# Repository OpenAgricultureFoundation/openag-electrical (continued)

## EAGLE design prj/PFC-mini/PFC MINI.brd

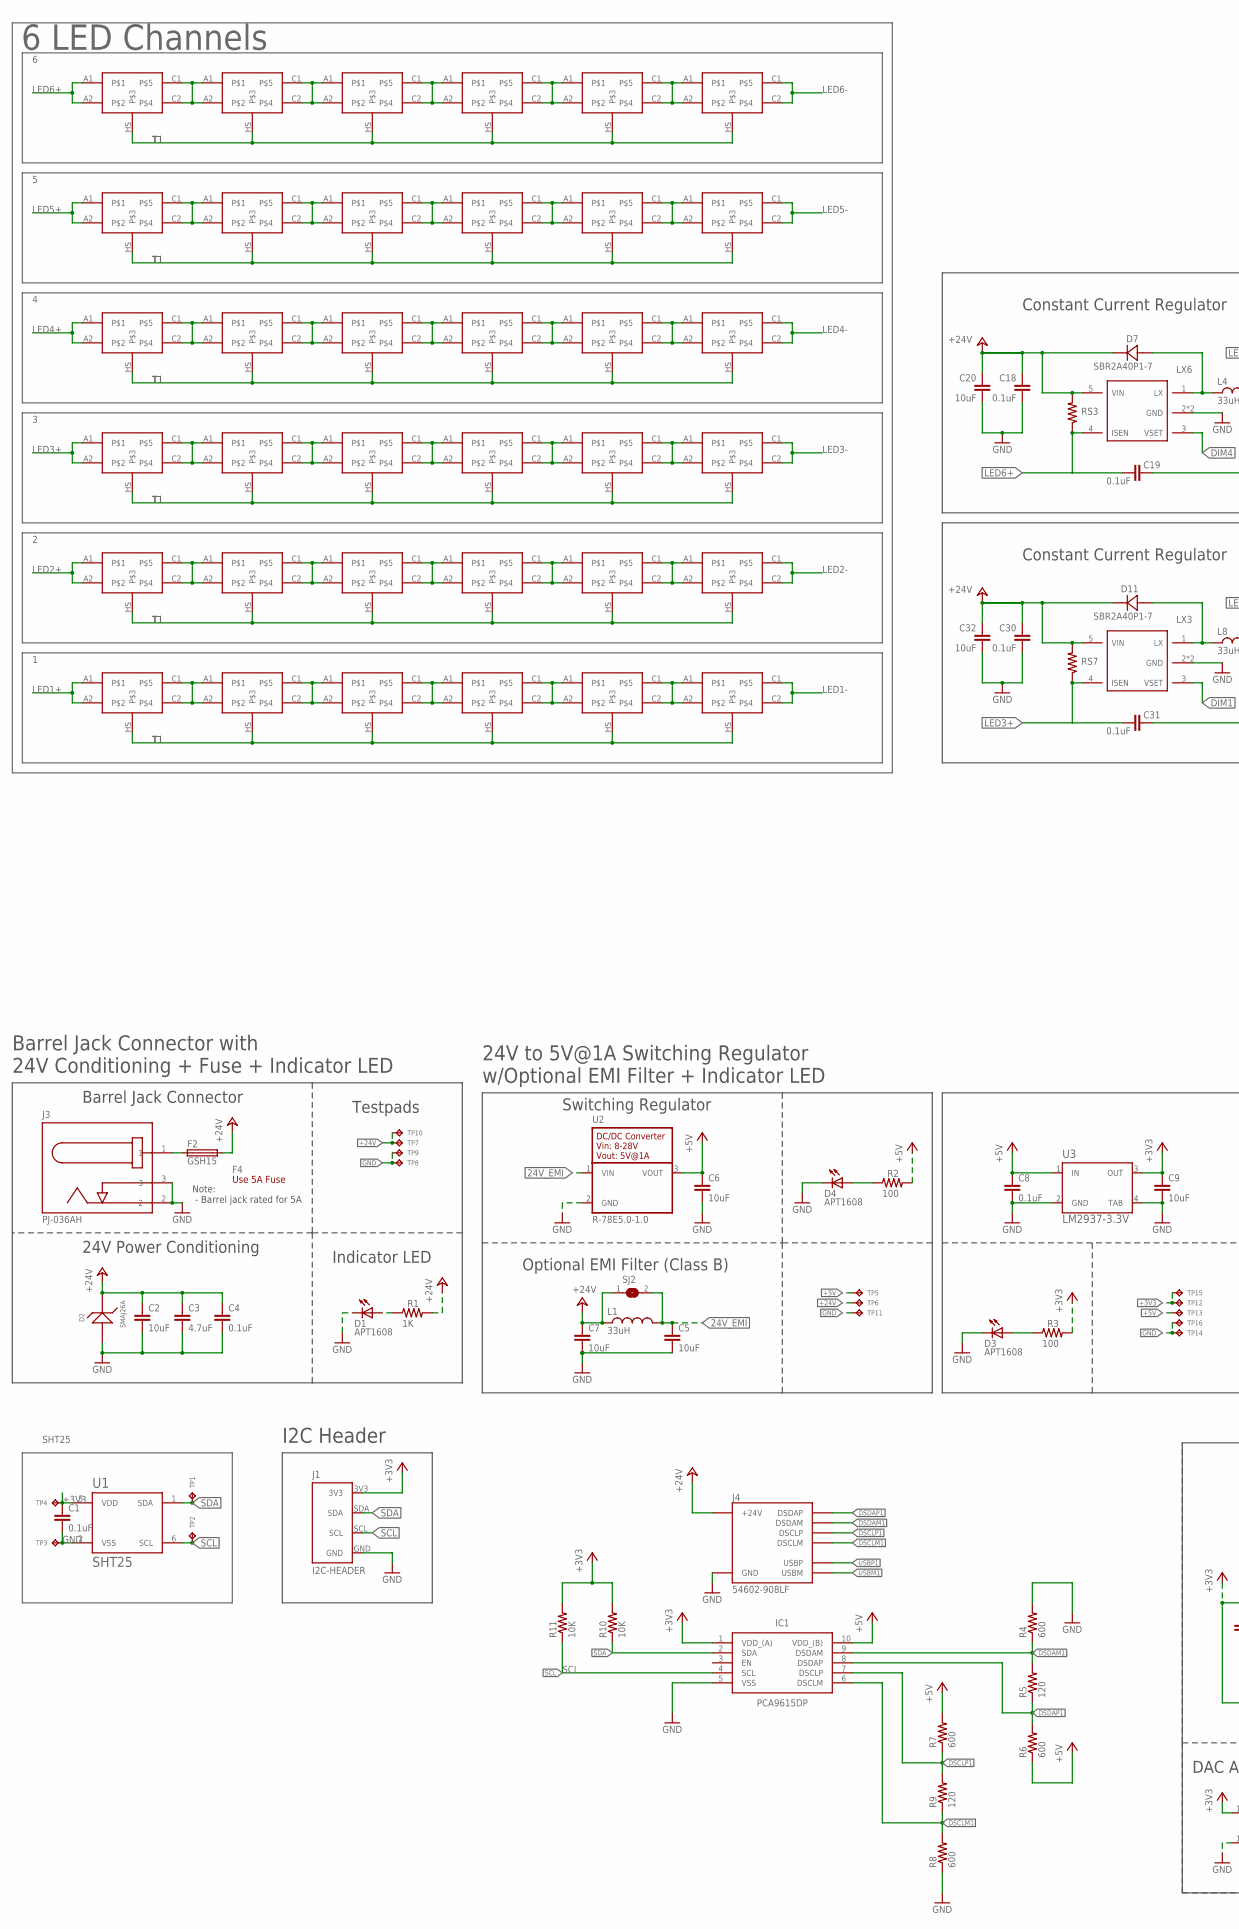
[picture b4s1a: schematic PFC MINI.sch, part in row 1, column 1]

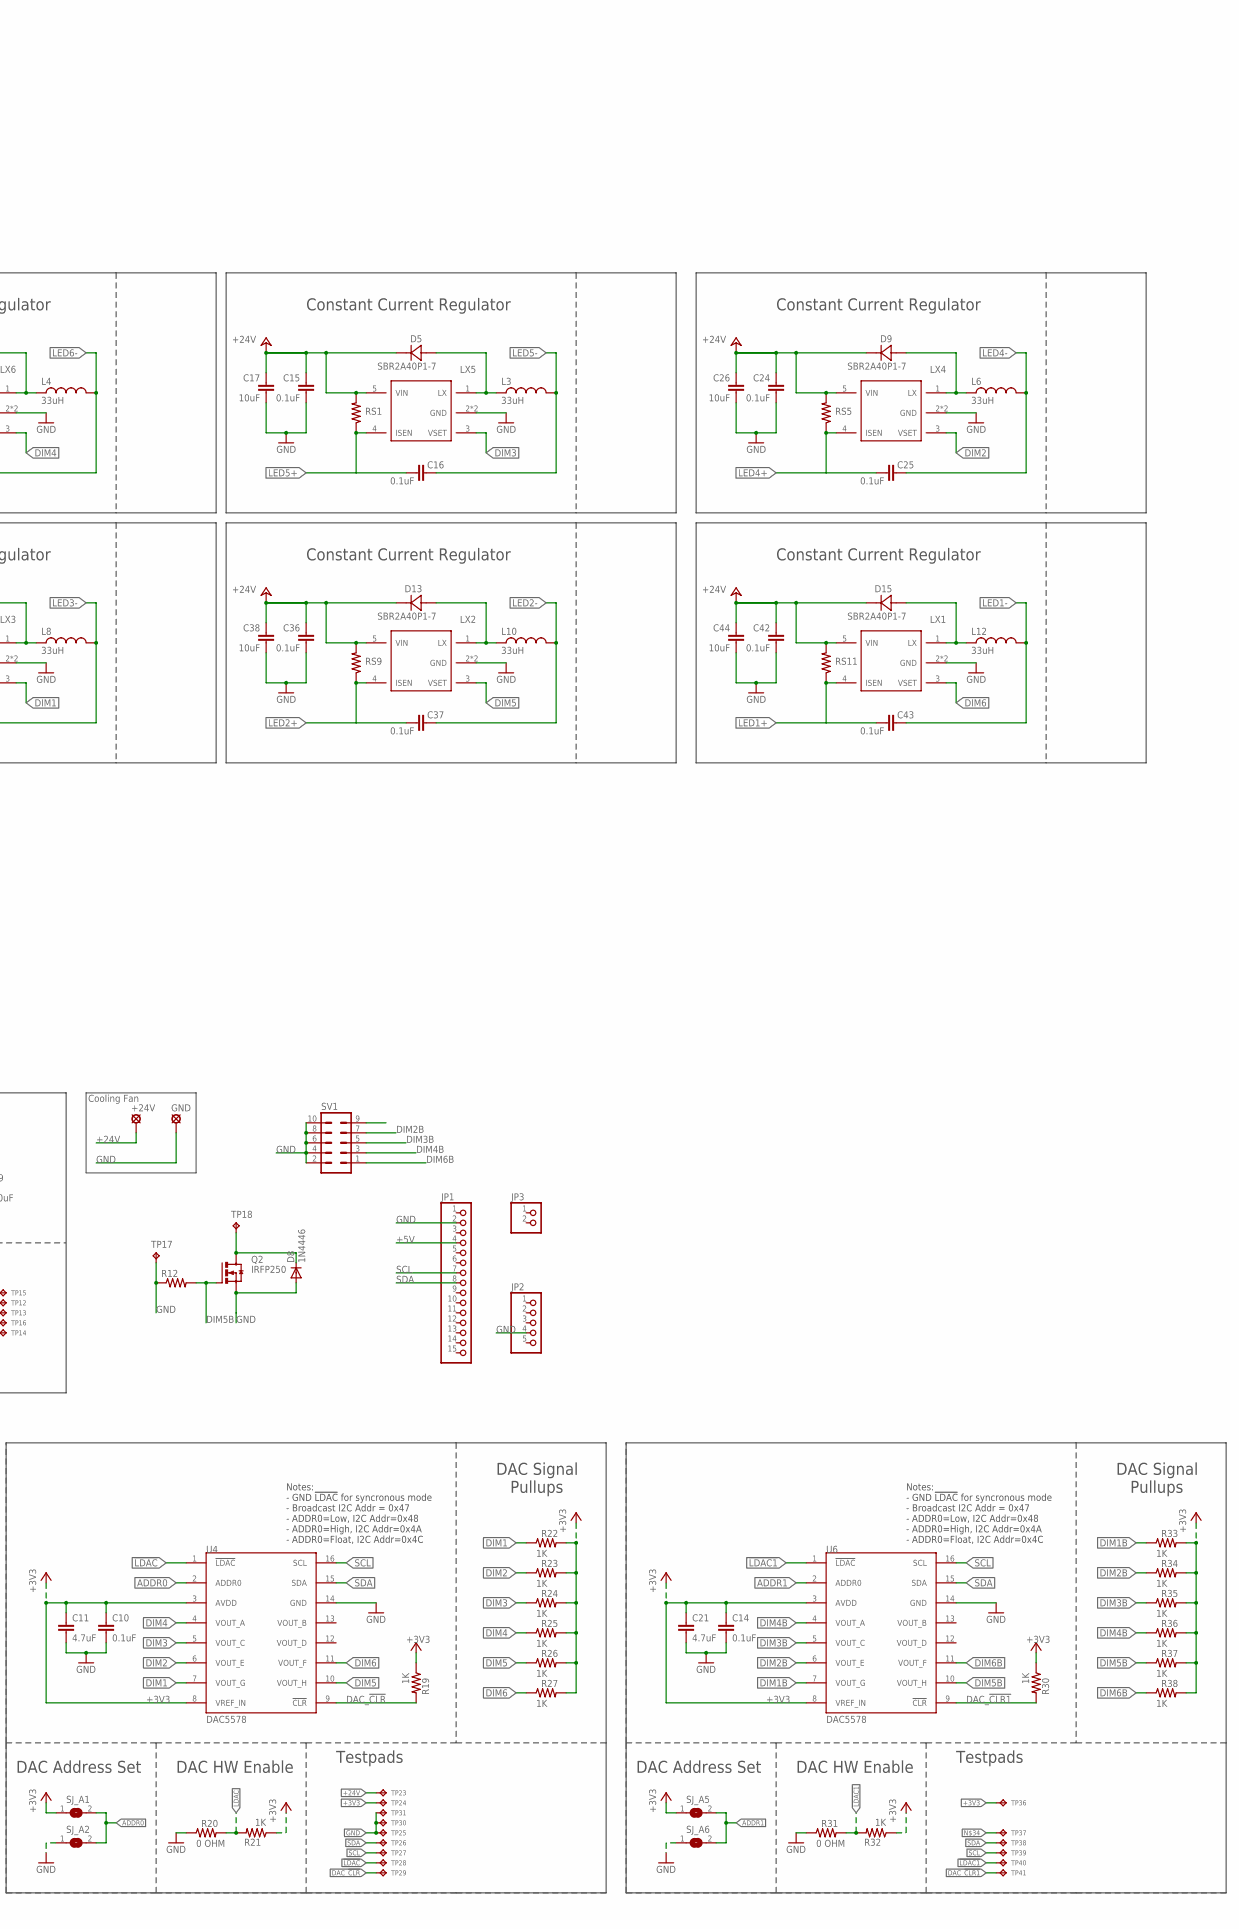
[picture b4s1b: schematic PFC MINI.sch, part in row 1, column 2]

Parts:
+24V: LSP10
C1, C4, C8, C10, C14, C15, C16, C18, C19, C24, C25, C30, C31, C36, C37, C42, C43: 0.1uF; C0603
C2, C5, C6, C7, C9, C17, C20, C26, C32, C38, C44: 10uF; C0805
C3, C11, C21: 4.7uF; C0805
D1, D3, D4: APT1608; CHIPLED_0603
D2: SMAJ26A; SMA
D5, D7, D9, D11, D13, D15: SBR2A40P1-7; POWERDI123
D8: 1N4446; DO35-10
F2: GSH15
F4: Use 5A Fuse; FUSE-CARTRIDGE
GND: LSP10
IC1: PCA9615DP; SOP50P490X110-10N
J1: I2C-HEADER; HEADER-I2C
J3: PJ-036AH; BARREL-JACK-PJ-036AH
J4: 54602-908LF; OPENAG-V1-RJ45
JP1: PINHD-1X15; 1X15
JP2: PINHD-1X5; 1X05
JP3: PINHD-1X2; 1X02
L1, L3, L4, L6, L8, L10, L12: 33uH; 29333C
Q2: IRFP250; TO-247AD-V
R1, R19, R21, R22, R23, R24, R25, R26, R27, R30, R32, R33, R34, R35, R36, R37, R38: 1K; RC0603N
R2, R3: 100; RC0603N
R4, R6, R7, R8: 600; R0603
R5, R9: 120; R0603
R10, R11: 10K; R0603
R12: R-US_R0603; R0603
R20, R31: 0 OHM; RC0603N
RS1, RS5, RS7, RS9, RS11: 6.34 ohm; R0805
RS3: 0.66 ohm; R0805
SJ2: EMI-BYPASS
SJ_A1, SJ_A2, SJ_A5, SJ_A6: SOLDERJUMPERREFLOW_NOPASTE; SJ1
SV1: MA05-2
TP1, TP2, TP3, TP4, TP5, TP6, TP11: TPTP06R; TP06R
TP7, TP8, TP9, TP10, TP12, TP13, TP14, TP15, TP16, TP23, TP24, TP25, TP26, TP27, TP28, TP29, TP30, TP31, TP36, TP37, TP38, TP39, TP40, TP41: TPTP04R; TP04R
TP17, TP18: TPPAD1-13; P1-13
U1: SHT25; SHT2X
U2: R-78E5.0-1.0
U3: LM2937-3.3V; MP04A
U4, U6: DAC5578; TSSOP16
U$2, U$3, U$4, U$5, U$6, U$7, U$8, U$9, U$10, U$11, U$12, U$13, U$14, U$15, U$16, U$17, U$18, U$19, U$20, U$21, U$22, U$23, U$24, U$25, U$26, U$27, U$28, U$29, U$30, U$31, U$32, U$33, U$34, U$35, U$36, U$37: MLELED; MLELEDCREE
U$38, U$40, U$42, U$44, U$46, U$48: AL8861

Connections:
24V_EMI: C5.1, L1.2, SJ2.2, U2.1 (VIN)
24V_IN1: F2.1, J3.1
!LDAC1!: R31.2, R32.2, TP40.1, U6.1 (!LDAC!)
!LDAC!: R20.2, R21.2, TP28.1, U4.1 (!LDAC!)
+3V3: C1.1, C9.1, C10.1, C11.1, C14.1, C21.1, IC1.1 (VDD_(A)), J1.3V3, R3.2, R10.2, R11.2, R19.1, R21.1, R22.2, R23.2, R24.2, R25.2, R26.2, R27.2, R30.1, R32.1, R33.2, R34.2, R35.2, R36.2, R37.2, R38.2, SJ_A1.1, SJ_A5.1, TP4.TP, TP12.1, TP15.1, TP24.1, TP36.1, U1.5 (VDD), U3.3 (OUT), U4.3 (AVDD), U4.8 (VREF_IN), U6.3 (AVDD), U6.8 (VREF_IN)
+5V: C6.1, C8.1, IC1.10 (VDD_(B)), JP1.4, R2.2, R6.1, R7.2, TP5.TP, TP13.1, U2.3 (VOUT), U3.1 (IN)
+24V: +24V.MP, C2.1, C3.1, C4.1, C7.1, C15.1, C17.1, C18.1, C20.1, C24.1, C26.1, C30.1, C32.1, C36.1, C38.1, C42.1, C44.1, D2.1, D5.-, D7.-, D9.-, D11.-, D13.-, D15.-, F2.2, J4.24V(6) (+24V), L1.1, R1.2, RS1.2, RS3.2, RS5.2, RS7.2, RS9.2, RS11.2, SJ2.1, TP6.TP, TP7.1, TP10.1, TP23.1, U$38.5 (VIN), U$40.5 (VIN), U$42.5 (VIN), U$44.5 (VIN), U$46.5 (VIN), U$48.5 (VIN)
ADDR0: SJ_A1.2, SJ_A2.2, U4.2 (ADDR0)
ADDR1: SJ_A5.2, SJ_A6.2, U6.2 (ADDR0)
DAC_!CLR1!: R30.2, TP41.1, U6.9 (!CLR!)
DAC_!CLR!: R19.2, TP29.1, U4.9 (!CLR!)
DIM1: R22.1, U4.7 (VOUT_G), U$44.3 (VSET)
DIM1B: R33.1, U6.7 (VOUT_G)
DIM2: R23.1, U4.6 (VOUT_E), U$42.3 (VSET)
DIM2B: R34.1, SV1.7, U6.6 (VOUT_E)
DIM3: R24.1, U4.5 (VOUT_C), U$38.3 (VSET)
DIM3B: R35.1, SV1.5, U6.5 (VOUT_C)
DIM4: R25.1, U4.4 (VOUT_A), U$40.3 (VSET)
DIM4B: R36.1, SV1.3, U6.4 (VOUT_A)
DIM5: R26.1, U4.10 (VOUT_H), U$46.3 (VSET)
DIM5B: Q2.G, R12.2, R37.1, U6.10 (VOUT_H)
DIM6: R27.1, U4.11 (VOUT_F), U$48.3 (VSET)
DIM6B: R38.1, SV1.1, U6.11 (VOUT_F)
DSCLM1: IC1.6 (DSCLM), J4.DSCLM(5) (DSCLM), R8.2, R9.1
DSCLP1: IC1.7 (DSCLP), J4.DSCLP(4) (DSCLP), R7.1, R9.2
DSDAM1: IC1.9 (DSDAM), J4.DSDAM(2) (DSDAM), R4.1, R5.2
DSDAP1: IC1.8 (DSDAP), J4.DSDAP(1) (DSDAP), R5.1, R6.2
GND: C1.2, C2.2, C3.2, C4.2, C5.2, C6.2, C7.2, C8.2, C9.2, C10.2, C11.2, C14.2, C15.2, C17.2, C18.2, C20.2, C21.2, C24.2, C26.2, C30.2, C32.2, C36.2, C38.2, C42.2, C44.2, D1.C, D2.2, D3.C, D4.C, D8.A, GND.MP, IC1.5 (VSS), J1.GND, J3.2, J3.3, J4.GND(3) (GND), JP1.2, JP2.4, Q2.S, R4.2, R8.1, R12.1, R20.1, R31.1, SJ_A2.1, SJ_A6.1, SV1.2, SV1.4, SV1.6, SV1.8, SV1.10, TP3.TP, TP8.1, TP9.1, TP11.TP, TP14.1, TP16.1, TP17.TP, TP25.1, TP30.1, TP31.1, U1.2 (VSS), U2.2 (GND), U3.2 (GND), U3.4 (TAB), U4.14 (GND), U6.14 (GND), U$38.2 (GND), U$38.44 (GND), U$40.2 (GND), U$40.44 (GND), U$42.2 (GND), U$42.44 (GND), U$44.2 (GND), U$44.44 (GND), U$46.2 (GND), U$46.44 (GND), U$48.2 (GND), U$48.44 (GND)
LED1+: C43.2, RS11.1, U$2.A1, U$2.A2, U$48.4 (ISEN)
LED1-: C43.1, L12.2, U$7.C1, U$7.C2
LED2+: C37.2, RS9.1, U$8.A1, U$8.A2, U$46.4 (ISEN)
LED2-: C37.1, L10.2, U$13.C1, U$13.C2
LED3+: C31.2, RS7.1, U$14.A1, U$14.A2, U$44.4 (ISEN)
LED3-: C31.1, L8.2, U$19.C1, U$19.C2
LED4+: C25.2, RS5.1, U$20.A1, U$20.A2, U$42.4 (ISEN)
LED4-: C25.1, L6.2, U$25.C1, U$25.C2
LED5+: C16.2, RS1.1, U$26.A1, U$26.A2, U$38.4 (ISEN)
LED5-: C16.1, L3.2, U$31.C1, U$31.C2
LED6+: C19.2, RS3.1, U$32.A1, U$32.A2, U$40.4 (ISEN)
LED6-: C19.1, L4.2, U$37.C1, U$37.C2
LX1: D15.+, L12.1, U$48.1 (LX)
LX2: D13.+, L10.1, U$46.1 (LX)
LX3: D11.+, L8.1, U$44.1 (LX)
LX4: D9.+, L6.1, U$42.1 (LX)
LX5: D5.+, L3.1, U$38.1 (LX)
LX6: D7.+, L4.1, U$40.1 (LX)
unnamed: D1.A, R1.1
unnamed: U$2.C1, U$2.C2, U$3.A1, U$3.A2
unnamed: D4.A, R2.1
unnamed: D3.A, R3.1
unnamed: U$8.C1, U$8.C2, U$9.A1, U$9.A2
unnamed: U$3.C1, U$3.C2, U$4.A1, U$4.A2
unnamed: U$9.C1, U$9.C2, U$10.A1, U$10.A2
unnamed: U$4.C1, U$4.C2, U$5.A1, U$5.A2
unnamed: U$10.C1, U$10.C2, U$11.A1, U$11.A2
unnamed: U$5.C1, U$5.C2, U$6.A1, U$6.A2
unnamed: U$6.C1, U$6.C2, U$7.A1, U$7.A2
unnamed: U$11.C1, U$11.C2, U$12.A1, U$12.A2
unnamed: U$12.C1, U$12.C2, U$13.A1, U$13.A2
unnamed: U$14.C1, U$14.C2, U$15.A1, U$15.A2
unnamed: U$15.C1, U$15.C2, U$16.A1, U$16.A2
unnamed: U$16.C1, U$16.C2, U$17.A1, U$17.A2
unnamed: U$17.C1, U$17.C2, U$18.A1, U$18.A2
unnamed: U$18.C1, U$18.C2, U$19.A1, U$19.A2
unnamed: U$20.C1, U$20.C2, U$21.A1, U$21.A2
unnamed: U$21.C1, U$21.C2, U$22.A1, U$22.A2
unnamed: U$22.C1, U$22.C2, U$23.A1, U$23.A2
unnamed: U$23.C1, U$23.C2, U$24.A1, U$24.A2
unnamed: U$24.C1, U$24.C2, U$25.A1, U$25.A2
unnamed: U$26.C1, U$26.C2, U$27.A1, U$27.A2
unnamed: U$27.C1, U$27.C2, U$28.A1, U$28.A2
unnamed: U$28.C1, U$28.C2, U$29.A1, U$29.A2
unnamed: U$29.C1, U$29.C2, U$30.A1, U$30.A2
unnamed: U$30.C1, U$30.C2, U$31.A1, U$31.A2
unnamed: U$32.C1, U$32.C2, U$33.A1, U$33.A2
unnamed: U$33.C1, U$33.C2, U$34.A1, U$34.A2
unnamed: U$34.C1, U$34.C2, U$35.A1, U$35.A2
unnamed: U$35.C1, U$35.C2, U$36.A1, U$36.A2
unnamed: U$36.C1, U$36.C2, U$37.A1, U$37.A2
unnamed: D8.C, Q2.D, TP18.TP
SCL: IC1.4 (SCL), J1.SCL, JP1.7, R11.1, TP2.TP, TP27.1, TP39.1, U1.6 (SCL), U4.16 (SCL), U6.16 (SCL)
SDA: IC1.2 (SDA), J1.SDA, JP1.8, R10.1, TP1.TP, TP26.1, TP38.1, U1.1 (SDA), U4.15 (SDA), U6.15 (SDA)
T1: U$2.HS, U$3.HS, U$4.HS, U$5.HS, U$6.HS, U$7.HS, U$8.HS, U$9.HS, U$10.HS, U$11.HS, U$12.HS, U$13.HS, U$14.HS, U$15.HS, U$16.HS, U$17.HS, U$18.HS, U$19.HS, U$20.HS, U$21.HS, U$22.HS, U$23.HS, U$24.HS, U$25.HS, U$26.HS, U$27.HS, U$28.HS, U$29.HS, U$30.HS, U$31.HS, U$32.HS, U$33.HS, U$34.HS, U$35.HS, U$36.HS, U$37.HS
USBM1: J4.USBM(8) (USBM)
USBP1: J4.USBP(7) (USBP)

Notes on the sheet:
I2C Header
SHT25
Barrel Jack Connector
Barrel Jack Connector with 24V Conditioning + Fuse + Indicator LED
24V Power Conditioning
Indicator LED
Testpads
Note: - Barrel jack rated for 5A
24V to 5V@1A Switching Regulator w/Optional EMI Filter + Indicator LED
Switching Regulator
Optional EMI Filter (Class B)
Notes: - GND !LDAC! for syncronous mode - Broadcast I2C Addr = 0x47 - ADDR0=Low, I2C Addr=0x48 - ADDR0=High, I2C Addr=0x4A - ADDR0=Float, I2C Addr=0x4C
DAC Signal Pullups
DAC Address Set
DAC HW Enable
6 LED Channels
Constant Current Regulator
Cooling Fan

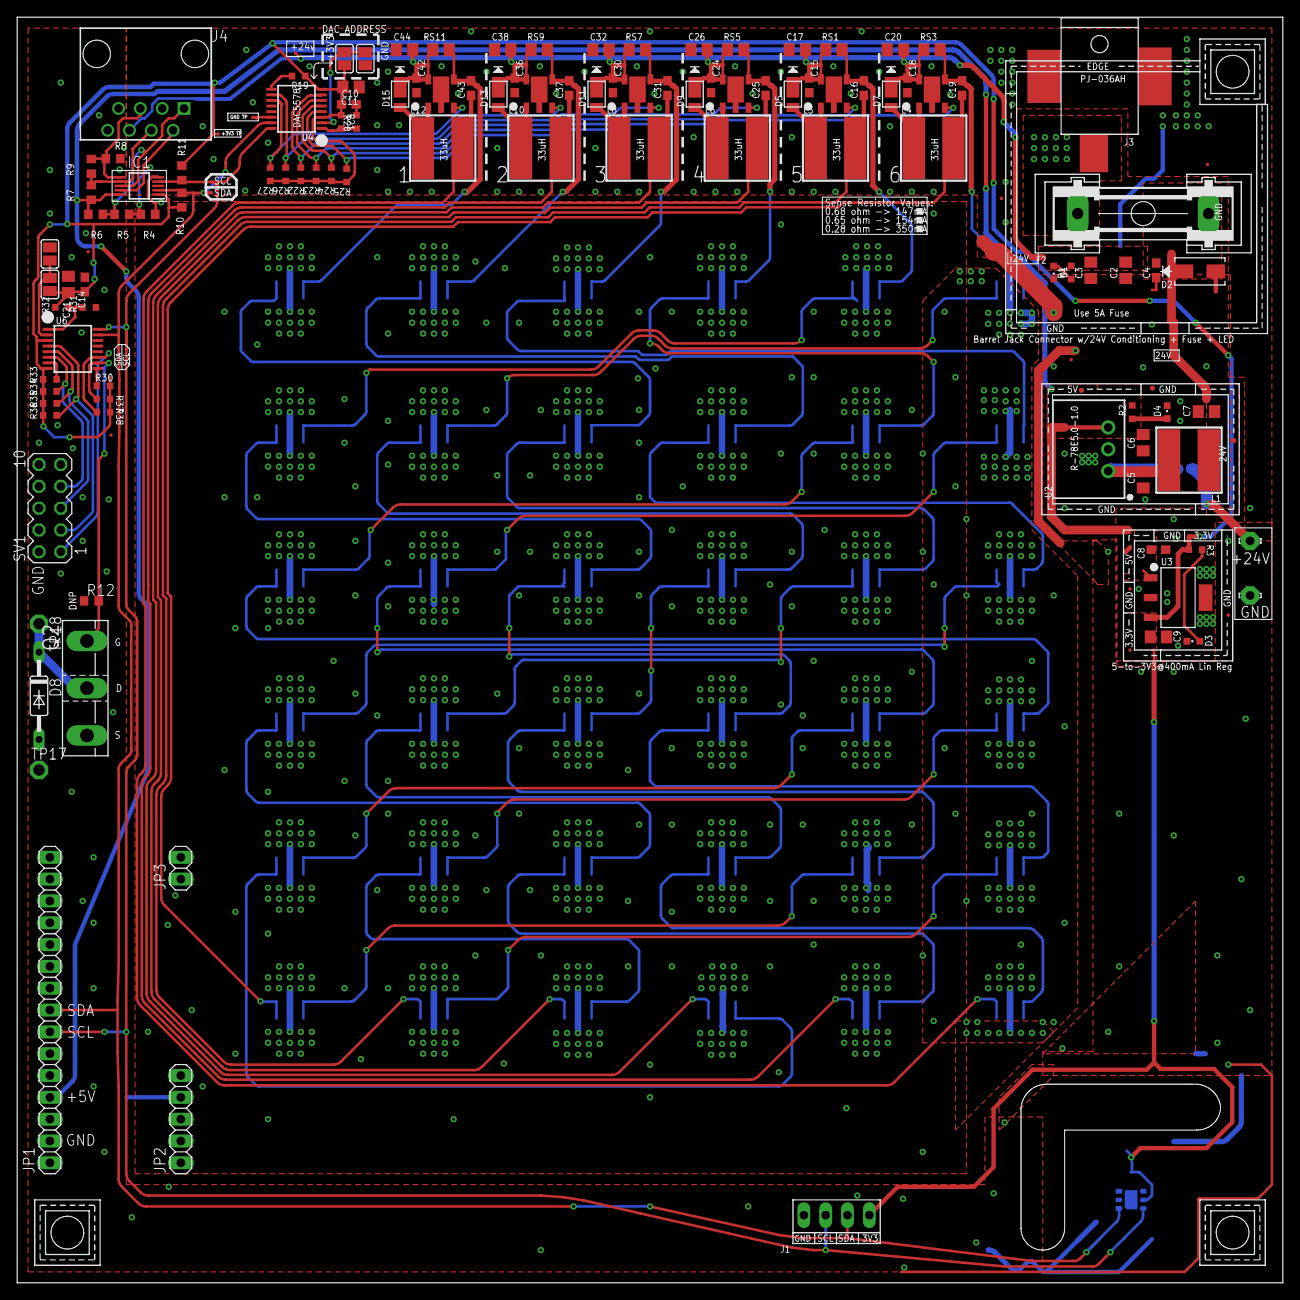
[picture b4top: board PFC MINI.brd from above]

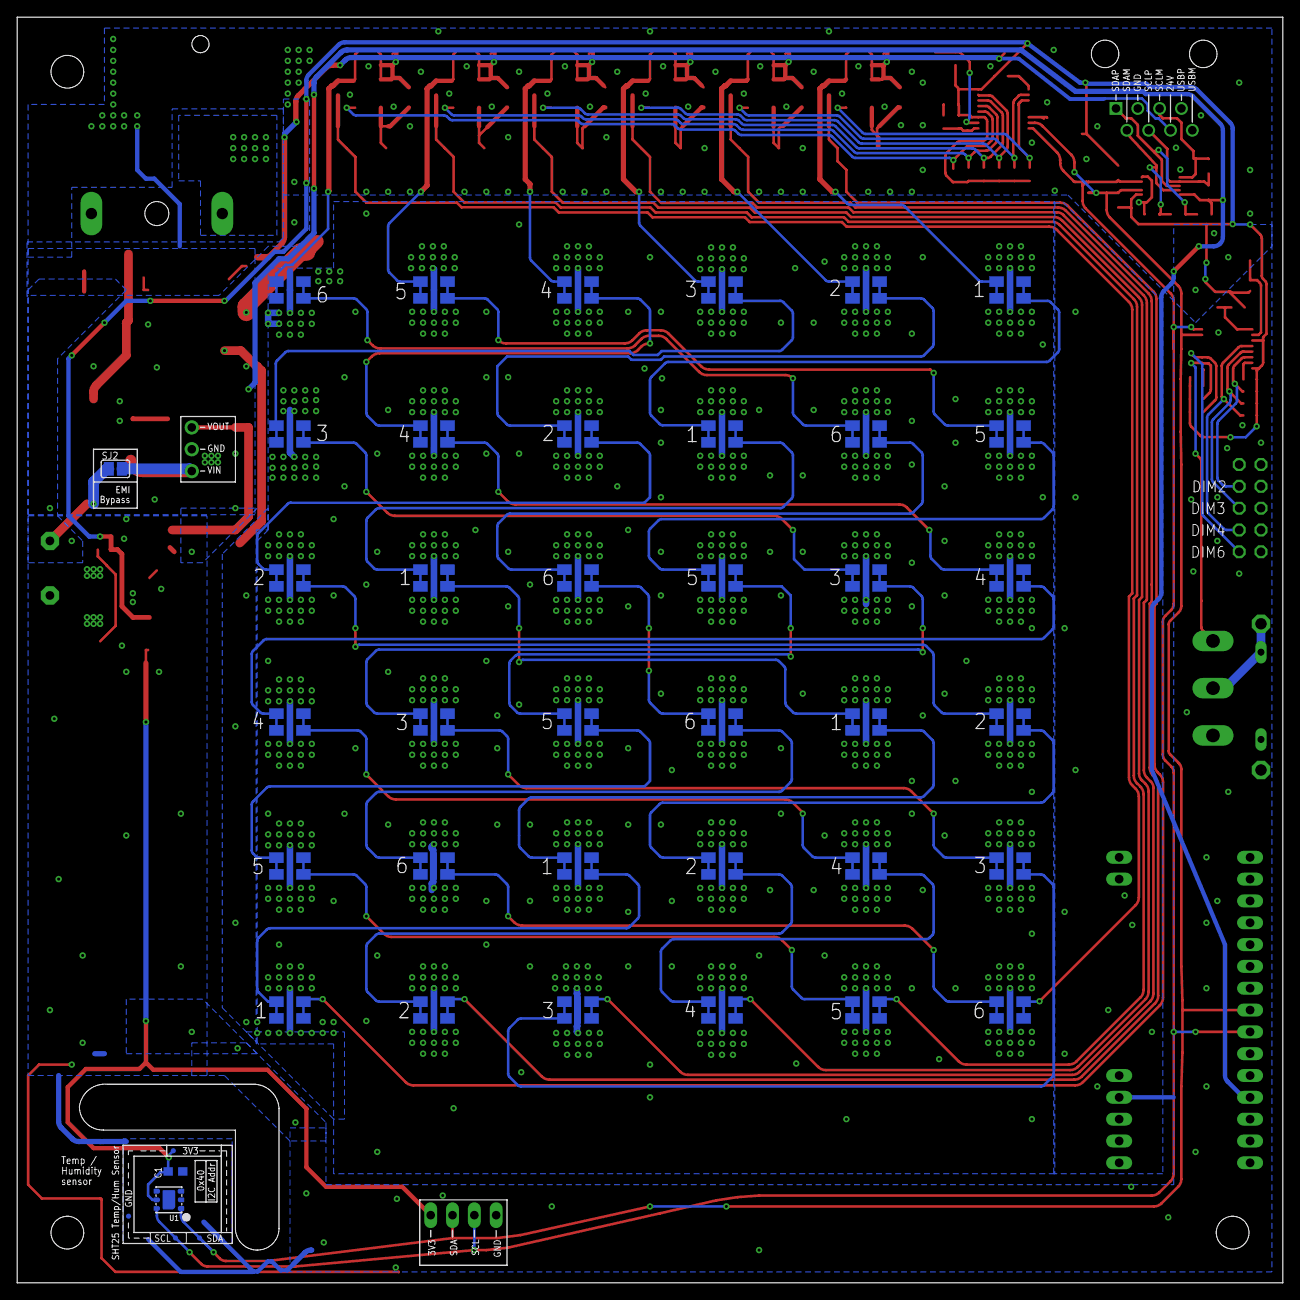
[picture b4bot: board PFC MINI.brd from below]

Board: 2 copper layers, 147.3 x 147.3 mm, 186 parts (43 on the bottom side), 83 nets.

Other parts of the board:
U$1, U$39, U$41: CORNER

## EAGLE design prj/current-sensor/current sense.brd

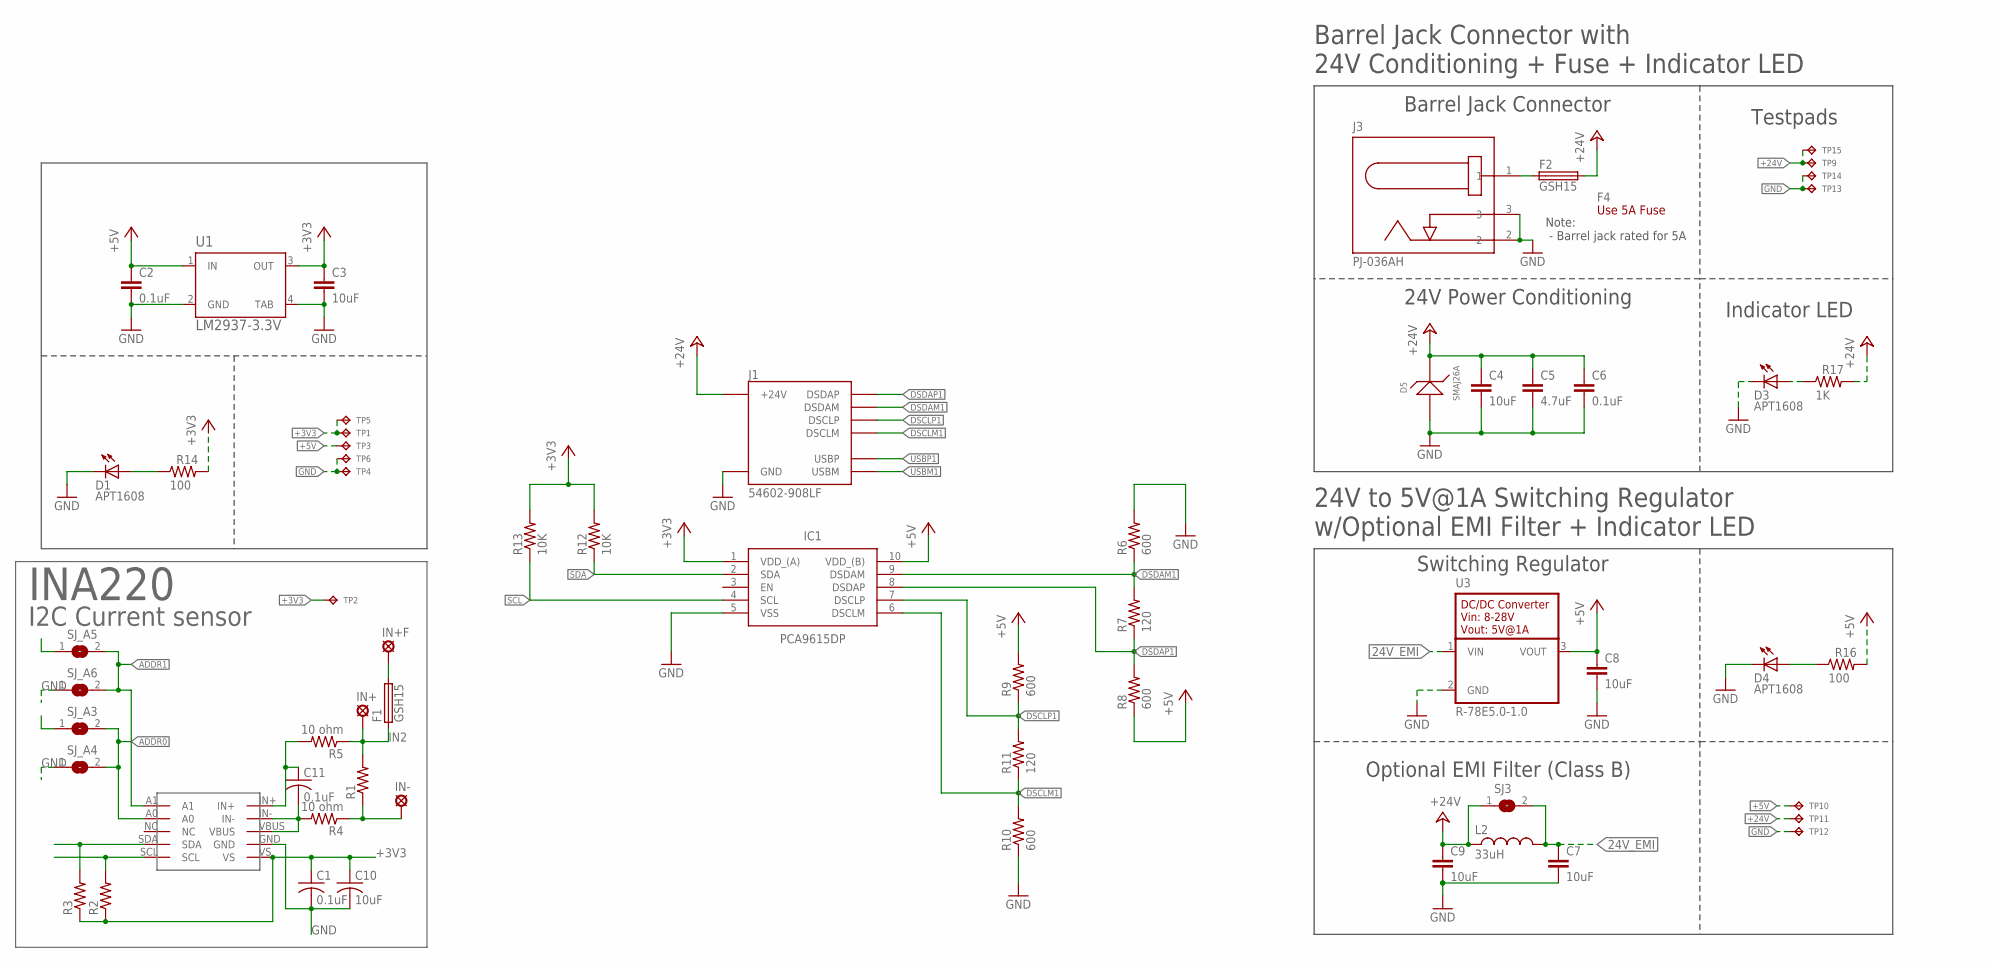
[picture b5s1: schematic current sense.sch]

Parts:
C1, C2, C6, C11: 0.1uF; C0603
C3, C4, C7, C8, C9: 10uF; C0805
C5: 4.7uF; C0805
C10: 10uF; C0603
D1, D3, D4: APT1608; CHIPLED_0603
D5: SMAJ26A; SMA
F1, F2: GSH15
F4: Use 5A Fuse; FUSE-CARTRIDGE
IC1: PCA9615DP; SOP50P490X110-10N
IN+: LSP11
IN+F: LSP11
IN-: LSP11
J1: 54602-908LF; OPENAG-V1-RJ45
J3: PJ-036AH; BARREL-JACK-PJ-036AH
L2: 33uH; 29333C
R1: R-US_R0805; R0805
R2, R3: R-US_R0603; R0603
R4, R5: 10 ohm; R0603
R6, R8, R9, R10: 600; R0603
R7, R11: 120; R0603
R12, R13: 10K; R0603
R14, R16: 100; RC0603N
R17: 1K; RC0603N
SJ3: EMI-BYPASS
SJ_A3, SJ_A4, SJ_A5, SJ_A6: SOLDERJUMPERREFLOW_NOPASTE; SJ1
TP1, TP2, TP3, TP4, TP5, TP6, TP9, TP13, TP14, TP15: TPTP04R; TP04R
TP10, TP11, TP12: TPTP06R; TP06R
U1: LM2937-3.3V; MP04A
U3: R-78E5.0-1.0
U$1: INA220; VSSOP10

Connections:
24V_EMI: C7.1, L2.2, SJ3.2, U3.1 (VIN)
24V_IN1: F2.1, J3.1
+3V3: C1.1, C3.1, C10.1, IC1.1 (VDD_(A)), R2.1, R3.1, R12.2, R13.2, R14.2, SJ_A3.1, SJ_A5.1, TP1.1, TP2.1, TP5.1, U1.3 (OUT), U$1.VS
+5V: C2.1, C8.1, IC1.10 (VDD_(B)), R8.1, R9.2, R16.2, TP3.1, TP10.TP, U1.1 (IN), U3.3 (VOUT)
+24V: C4.1, C5.1, C6.1, C9.1, D5.1, F2.2, J1.24V(6) (+24V), L2.1, R17.2, SJ3.1, TP9.1, TP11.TP, TP15.1
ADDR0: SJ_A3.2, SJ_A4.2, U$1.A0
ADDR1: SJ_A5.2, SJ_A6.2, U$1.A1
DSCLM1: IC1.6 (DSCLM), J1.DSCLM(5) (DSCLM), R10.2, R11.1
DSCLP1: IC1.7 (DSCLP), J1.DSCLP(4) (DSCLP), R9.1, R11.2
DSDAM1: IC1.9 (DSDAM), J1.DSDAM(2) (DSDAM), R6.1, R7.2
DSDAP1: IC1.8 (DSDAP), J1.DSDAP(1) (DSDAP), R7.1, R8.2
GND: C1.2, C2.2, C3.2, C4.2, C5.2, C6.2, C7.2, C8.2, C9.2, C10.2, D1.C, D3.C, D4.C, D5.2, IC1.5 (VSS), J1.GND(3) (GND), J3.2, J3.3, R6.2, R10.1, SJ_A4.1, SJ_A6.1, TP4.1, TP6.1, TP12.TP, TP13.1, TP14.1, U1.2 (GND), U1.4 (TAB), U3.2 (GND), U$1.GND
IN2: F1.1, IN+.MP, R1.2, R5.1
unnamed: F1.2, IN+F.MP
unnamed: C11.2, R4.2, U$1.IN-, U$1.VBUS
unnamed: C11.1, R5.2, U$1.IN+
unnamed: IN-.MP, R1.1, R4.1
unnamed: D1.A, R14.1
unnamed: D3.A, R17.1
unnamed: D4.A, R16.1
SCL: IC1.4 (SCL), R2.2, R13.1, U$1.SCL
SDA: IC1.2 (SDA), R3.2, R12.1, U$1.SDA
USBM1: J1.USBM(8) (USBM)
USBP1: J1.USBP(7) (USBP)

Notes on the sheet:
I2C Current sensor
INA220
24V to 5V@1A Switching Regulator w/Optional EMI Filter + Indicator LED
Switching Regulator
Optional EMI Filter (Class B)
Barrel Jack Connector
Barrel Jack Connector with 24V Conditioning + Fuse + Indicator LED
24V Power Conditioning
Indicator LED
Testpads
Note: - Barrel jack rated for 5A

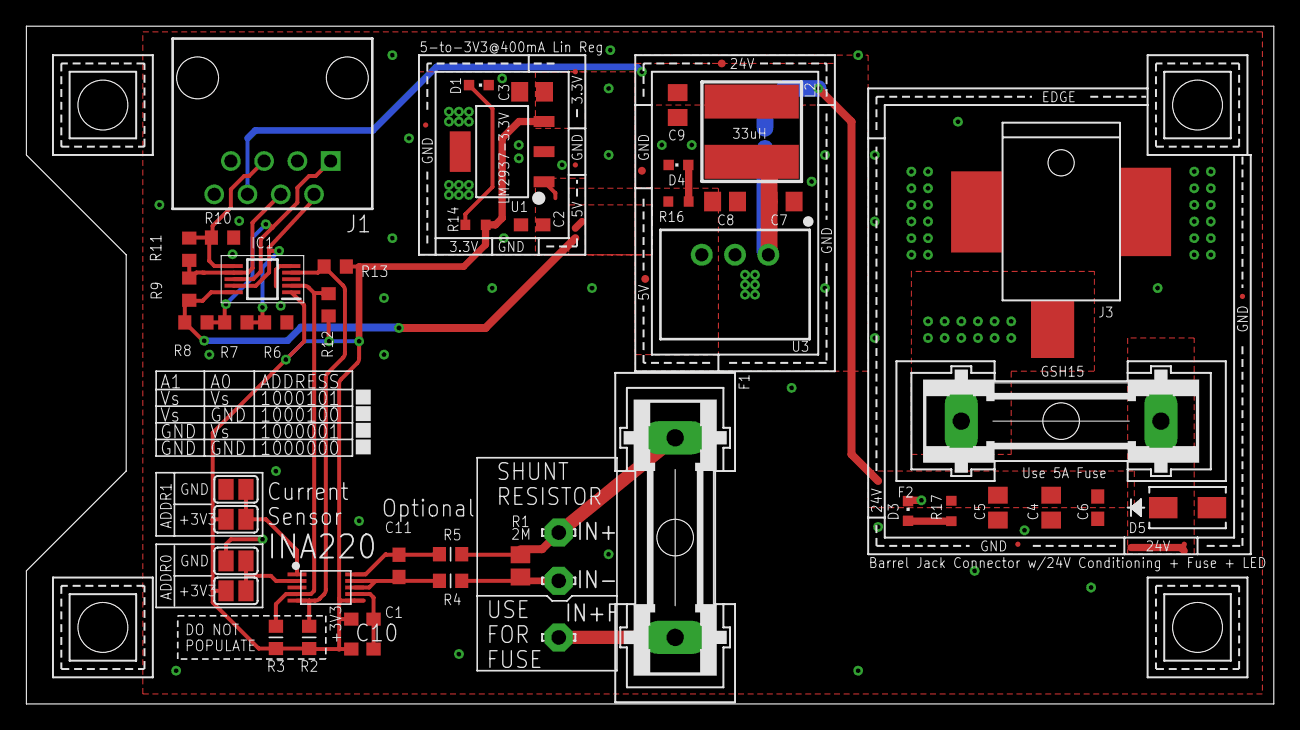
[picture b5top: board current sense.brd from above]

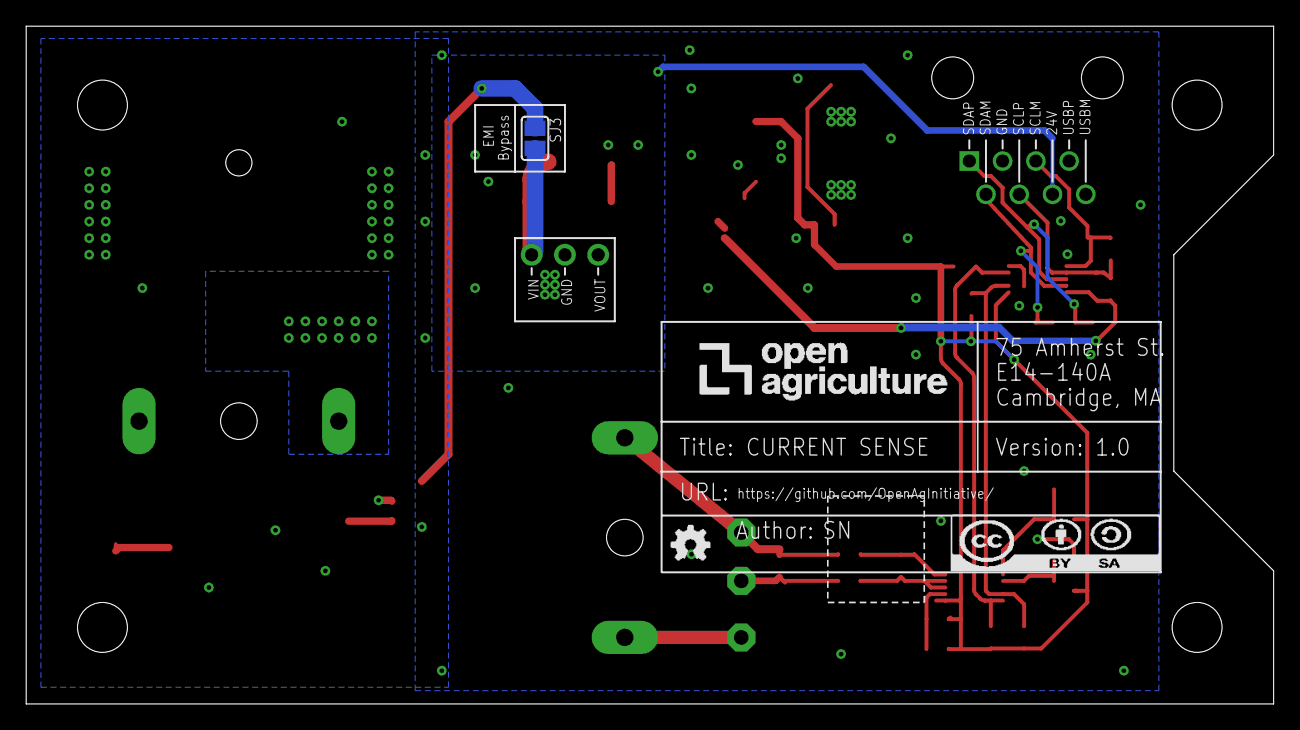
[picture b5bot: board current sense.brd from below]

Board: 2 copper layers, 95.2 x 51.7 mm, 67 parts (2 on the bottom side), 22 nets.

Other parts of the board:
ATTRIBUTES: DOCFIELD
U$2, U$3, U$4, U$5: CORNER

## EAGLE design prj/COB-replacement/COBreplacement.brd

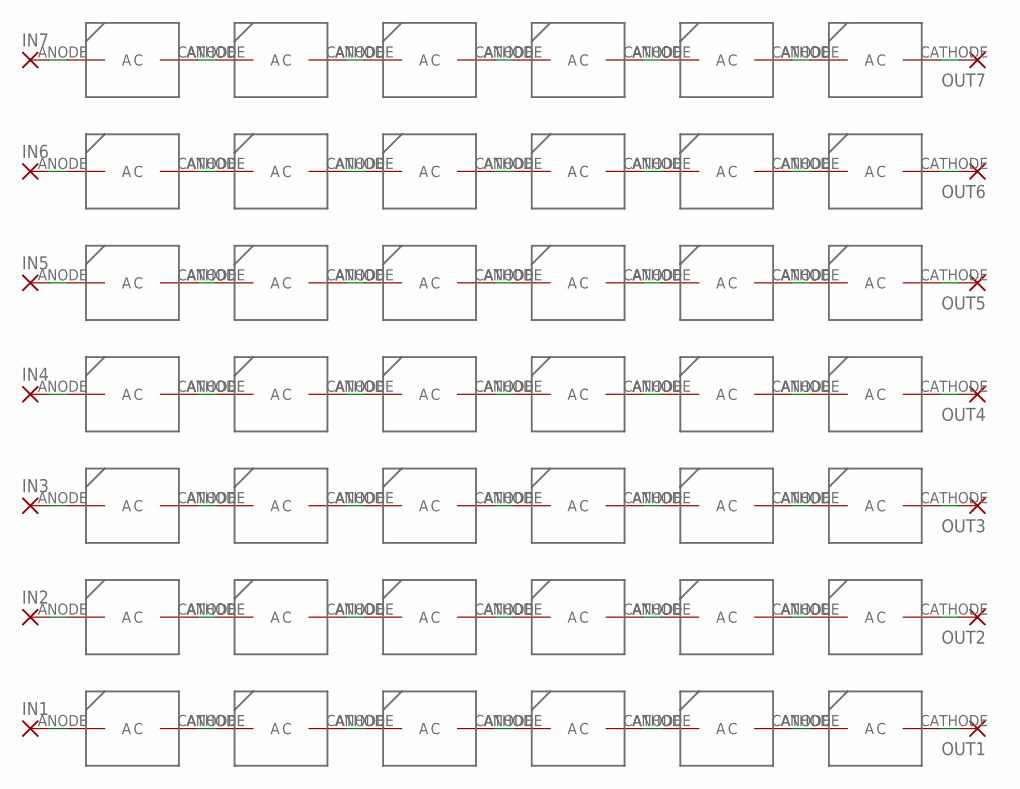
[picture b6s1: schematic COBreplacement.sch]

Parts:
IN1, IN2, IN3, IN4, IN5, IN6, IN7: SMD2; SMD1,27-2,54
OUT1, OUT2, OUT3, OUT4, OUT5, OUT6, OUT7: SMD2; SMD1,27-2,54
U$1, U$2, U$3, U$4, U$5, U$6, U$7, U$8, U$9, U$10, U$11, U$12, U$13, U$14, U$15, U$16, U$17, U$18, U$19, U$20, U$21, U$22, U$23, U$24, U$25, U$26, U$27, U$28, U$29, U$30, U$31, U$32, U$33, U$34, U$35, U$36, U$37, U$38, U$39, U$40, U$41, U$42: XPE35LED; XPE35

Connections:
unnamed: U$1.CATHODE (C), U$2.ANODE (A)
unnamed: U$2.CATHODE (C), U$3.ANODE (A)
unnamed: U$3.CATHODE (C), U$4.ANODE (A)
unnamed: U$4.CATHODE (C), U$5.ANODE (A)
unnamed: U$5.CATHODE (C), U$6.ANODE (A)
unnamed: IN6.1, U$1.ANODE (A)
unnamed: OUT6.1, U$6.CATHODE (C)
unnamed: U$7.CATHODE (C), U$8.ANODE (A)
unnamed: U$8.CATHODE (C), U$9.ANODE (A)
unnamed: U$9.CATHODE (C), U$10.ANODE (A)
unnamed: U$10.CATHODE (C), U$11.ANODE (A)
unnamed: U$11.CATHODE (C), U$12.ANODE (A)
unnamed: IN5.1, U$7.ANODE (A)
unnamed: OUT5.1, U$12.CATHODE (C)
unnamed: U$13.CATHODE (C), U$14.ANODE (A)
unnamed: U$14.CATHODE (C), U$15.ANODE (A)
unnamed: U$15.CATHODE (C), U$16.ANODE (A)
unnamed: U$16.CATHODE (C), U$17.ANODE (A)
unnamed: U$17.CATHODE (C), U$18.ANODE (A)
unnamed: IN4.1, U$13.ANODE (A)
unnamed: OUT4.1, U$18.CATHODE (C)
unnamed: U$19.CATHODE (C), U$20.ANODE (A)
unnamed: U$20.CATHODE (C), U$21.ANODE (A)
unnamed: U$21.CATHODE (C), U$22.ANODE (A)
unnamed: U$22.CATHODE (C), U$23.ANODE (A)
unnamed: U$23.CATHODE (C), U$24.ANODE (A)
unnamed: IN3.1, U$19.ANODE (A)
unnamed: OUT3.1, U$24.CATHODE (C)
unnamed: U$25.CATHODE (C), U$26.ANODE (A)
unnamed: U$26.CATHODE (C), U$27.ANODE (A)
unnamed: U$27.CATHODE (C), U$28.ANODE (A)
unnamed: U$28.CATHODE (C), U$29.ANODE (A)
unnamed: U$29.CATHODE (C), U$30.ANODE (A)
unnamed: IN2.1, U$25.ANODE (A)
unnamed: OUT2.1, U$30.CATHODE (C)
unnamed: U$31.CATHODE (C), U$32.ANODE (A)
unnamed: U$32.CATHODE (C), U$33.ANODE (A)
unnamed: U$33.CATHODE (C), U$34.ANODE (A)
unnamed: U$34.CATHODE (C), U$35.ANODE (A)
unnamed: U$35.CATHODE (C), U$36.ANODE (A)
unnamed: IN1.1, U$31.ANODE (A)
unnamed: OUT1.1, U$36.CATHODE (C)
unnamed: U$37.CATHODE (C), U$38.ANODE (A)
unnamed: U$38.CATHODE (C), U$39.ANODE (A)
unnamed: U$39.CATHODE (C), U$40.ANODE (A)
unnamed: U$40.CATHODE (C), U$41.ANODE (A)
unnamed: U$41.CATHODE (C), U$42.ANODE (A)
unnamed: IN7.1, U$37.ANODE (A)
unnamed: OUT7.1, U$42.CATHODE (C)

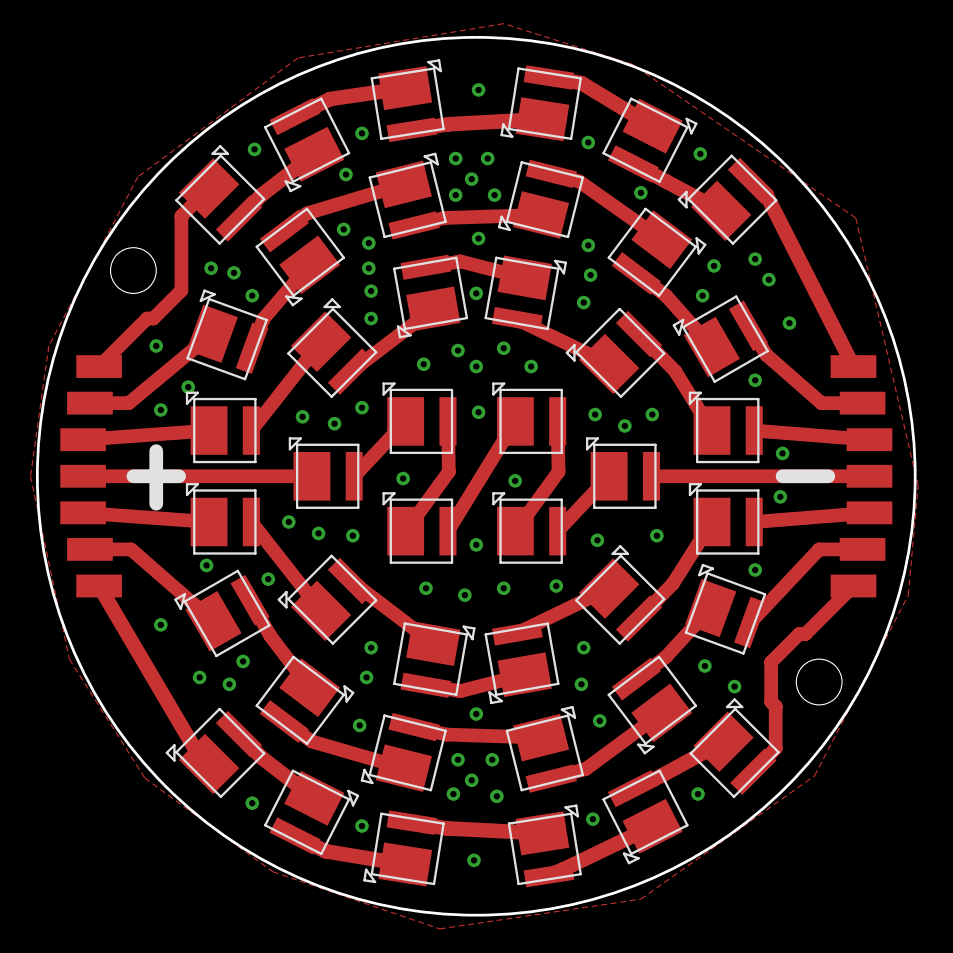
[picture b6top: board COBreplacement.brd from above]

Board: 2 copper layers, 48.8 x 48.8 mm, 56 parts (0 on the bottom side), 49 nets.
